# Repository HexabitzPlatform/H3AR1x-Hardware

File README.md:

# H3AR1x-Hardware
Hexabitz Module DIP Adapter/Hex Cut Hardware Design

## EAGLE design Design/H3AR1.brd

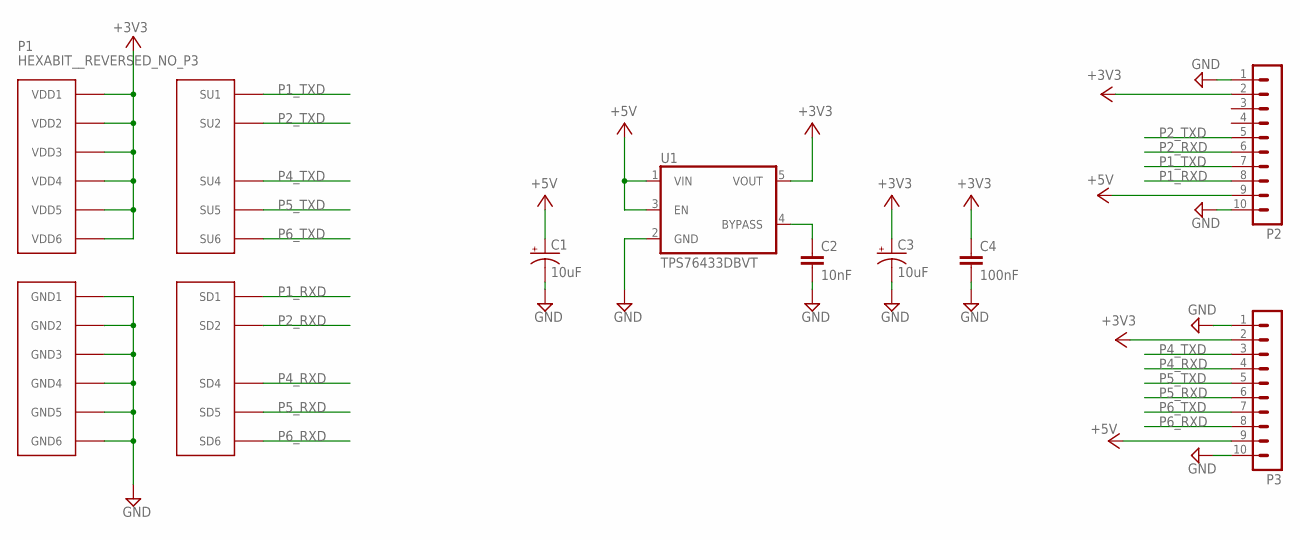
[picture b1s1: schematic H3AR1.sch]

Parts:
C1, C3: 10uF; C-1210-POL; MPN TPSB106K016R0500
C2: 10nF; C-0603; TOLERANCE 10%; VOLTAGE_RATING 50V; MPN C0603C103K5RACTU
C4: 100nF; C-0603; TOLERANCE 10%; VOLTAGE_RATING 10V; MPN C0603C104K8RACTU
P1: HEXABIT__REVERSED_NO_P3; HEXABIT_17.60_REVERSED_NO_P3
P2, P3: MA10-1; MPN 61301011121
TRIMBLE-LOGO1: HEXA-LOGO
U1: TPS76433DBVT; SOT25

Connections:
+3V3: C3.1 (+), C4.1, P1.PAD_PU7 (VDD1), P1.PAD_PU8 (VDD2), P1.PAD_PU9 (VDD3), P1.PAD_PU10 (VDD4), P1.PAD_PU11 (VDD5), P1.PAD_PU12 (VDD6), P2.2, P3.2, U1.5 (VOUT)
+5V: C1.1 (+), P2.9, P3.9, U1.1 (VIN), U1.3 (EN)
GND: C1.2 (-), C2.2, C3.2 (-), C4.2, P1.PAD_PD7 (GND1), P1.PAD_PD8 (GND2), P1.PAD_PD9 (GND3), P1.PAD_PD10 (GND4), P1.PAD_PD11 (GND5), P1.PAD_PD12 (GND6), P2.1, P2.10, P3.1, P3.10, U1.2 (GND)
unnamed: C2.1, U1.4 (BYPASS)
P1_RXD: P1.PAD_PD1 (SD1), P2.8
P1_TXD: P1.PAD_PU1 (SU1), P2.7
P2_RXD: P1.PAD_PD2 (SD2), P2.6
P2_TXD: P1.PAD_PU2 (SU2), P2.5
P4_RXD: P1.PAD_PD4 (SD4), P3.4
P4_TXD: P1.PAD_PU4 (SU4), P3.3
P5_RXD: P1.PAD_PD5 (SD5), P3.6
P5_TXD: P1.PAD_PU5 (SU5), P3.5
P6_RXD: P1.PAD_PD6 (SD6), P3.8
P6_TXD: P1.PAD_PU6 (SU6), P3.7

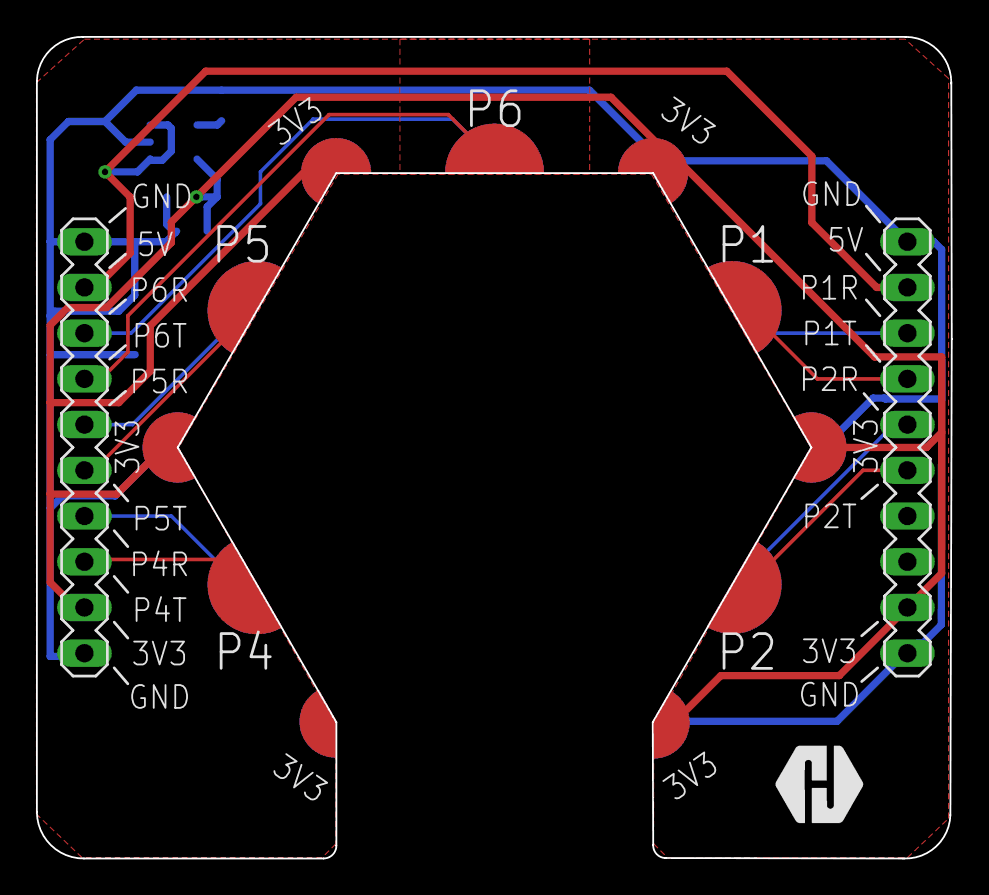
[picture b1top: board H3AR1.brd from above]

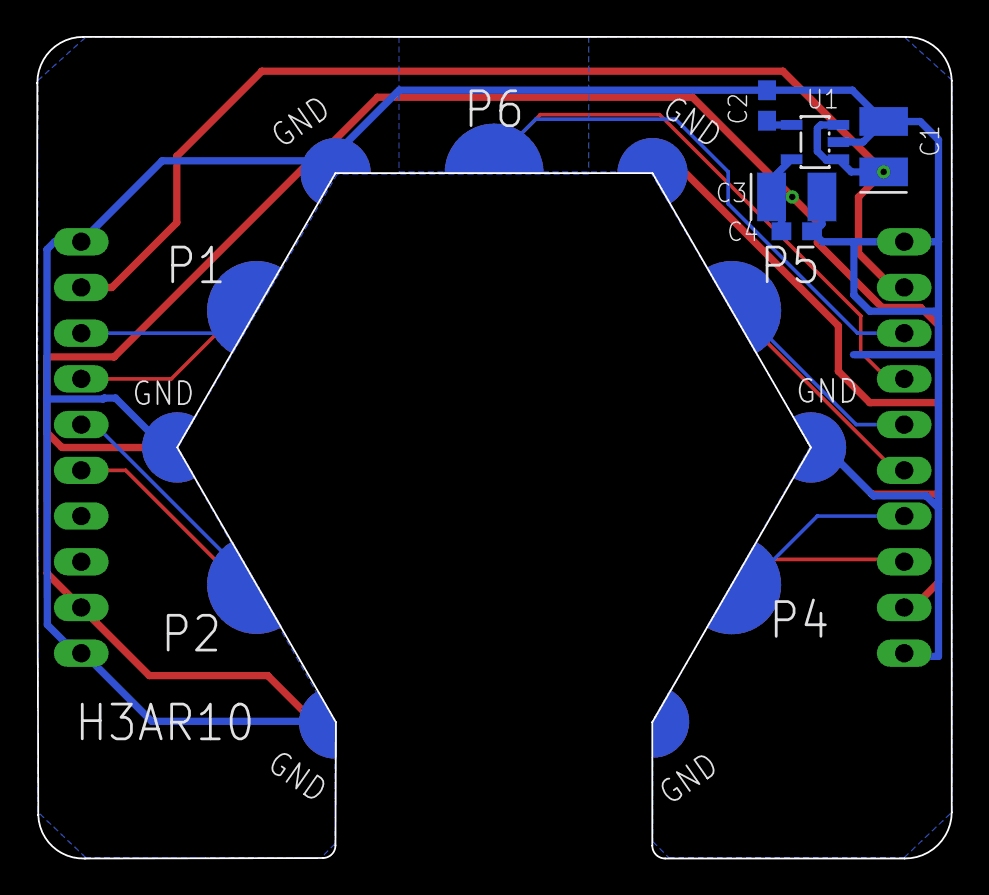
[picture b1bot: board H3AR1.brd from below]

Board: 2 copper layers, 50.8 x 45.6 mm, 9 parts (5 on the bottom side), 14 nets.

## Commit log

2024-03-25 All Finish, Reviewed Version
2024-03-26 Update the logo
